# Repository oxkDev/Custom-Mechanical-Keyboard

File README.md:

# Custom-Mechanical-Keyboard
A custom low-profile 75% mechanical keyboard using a WeAct Blackpill v3.1 (STM32F411CEU6).

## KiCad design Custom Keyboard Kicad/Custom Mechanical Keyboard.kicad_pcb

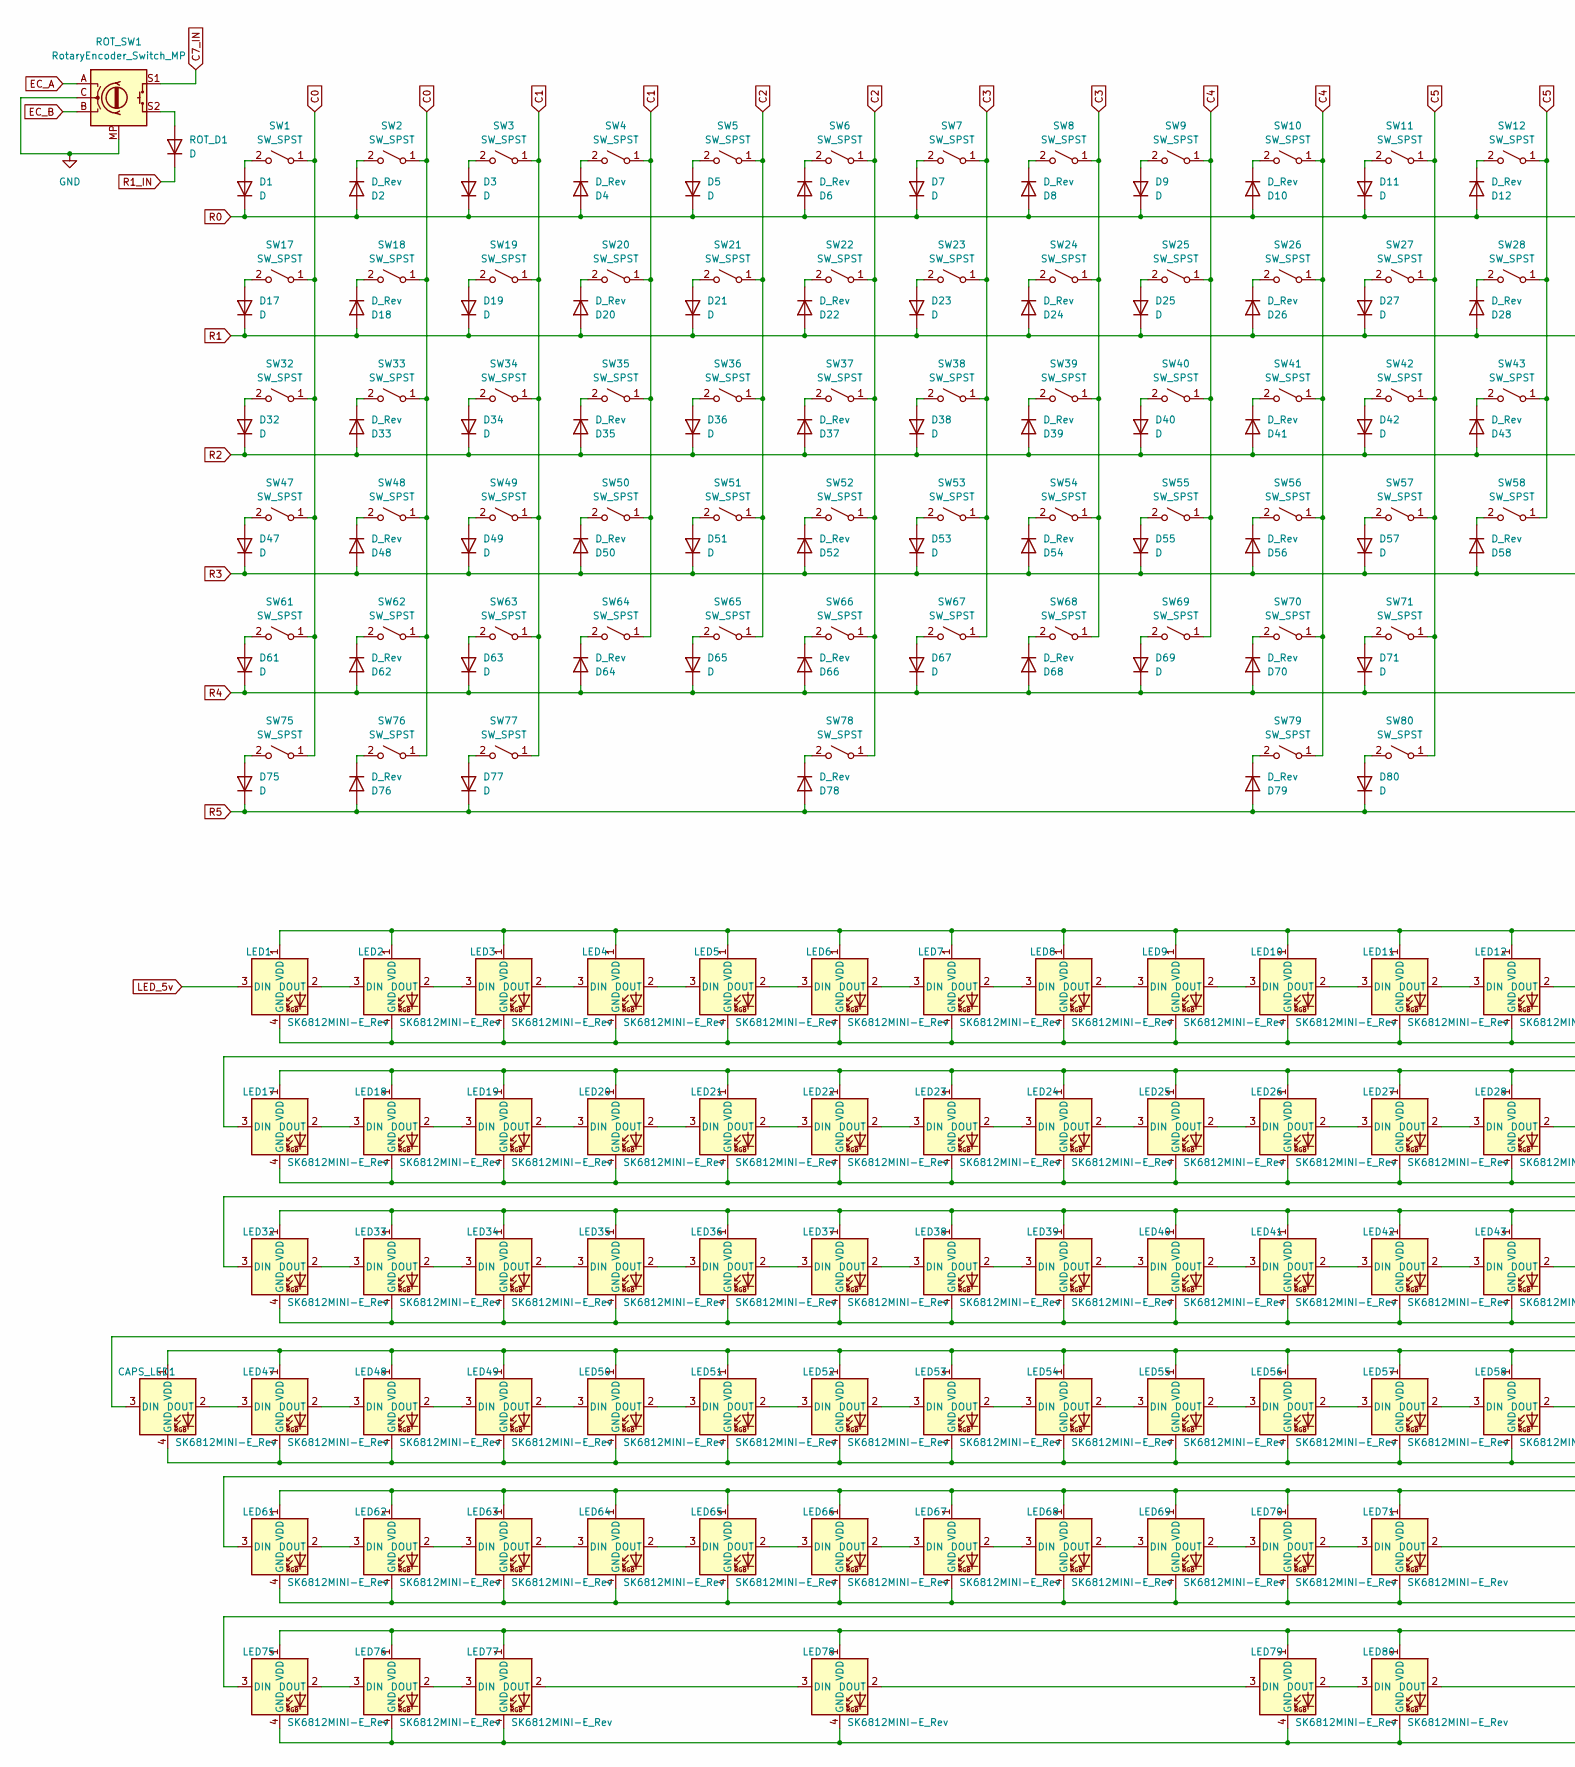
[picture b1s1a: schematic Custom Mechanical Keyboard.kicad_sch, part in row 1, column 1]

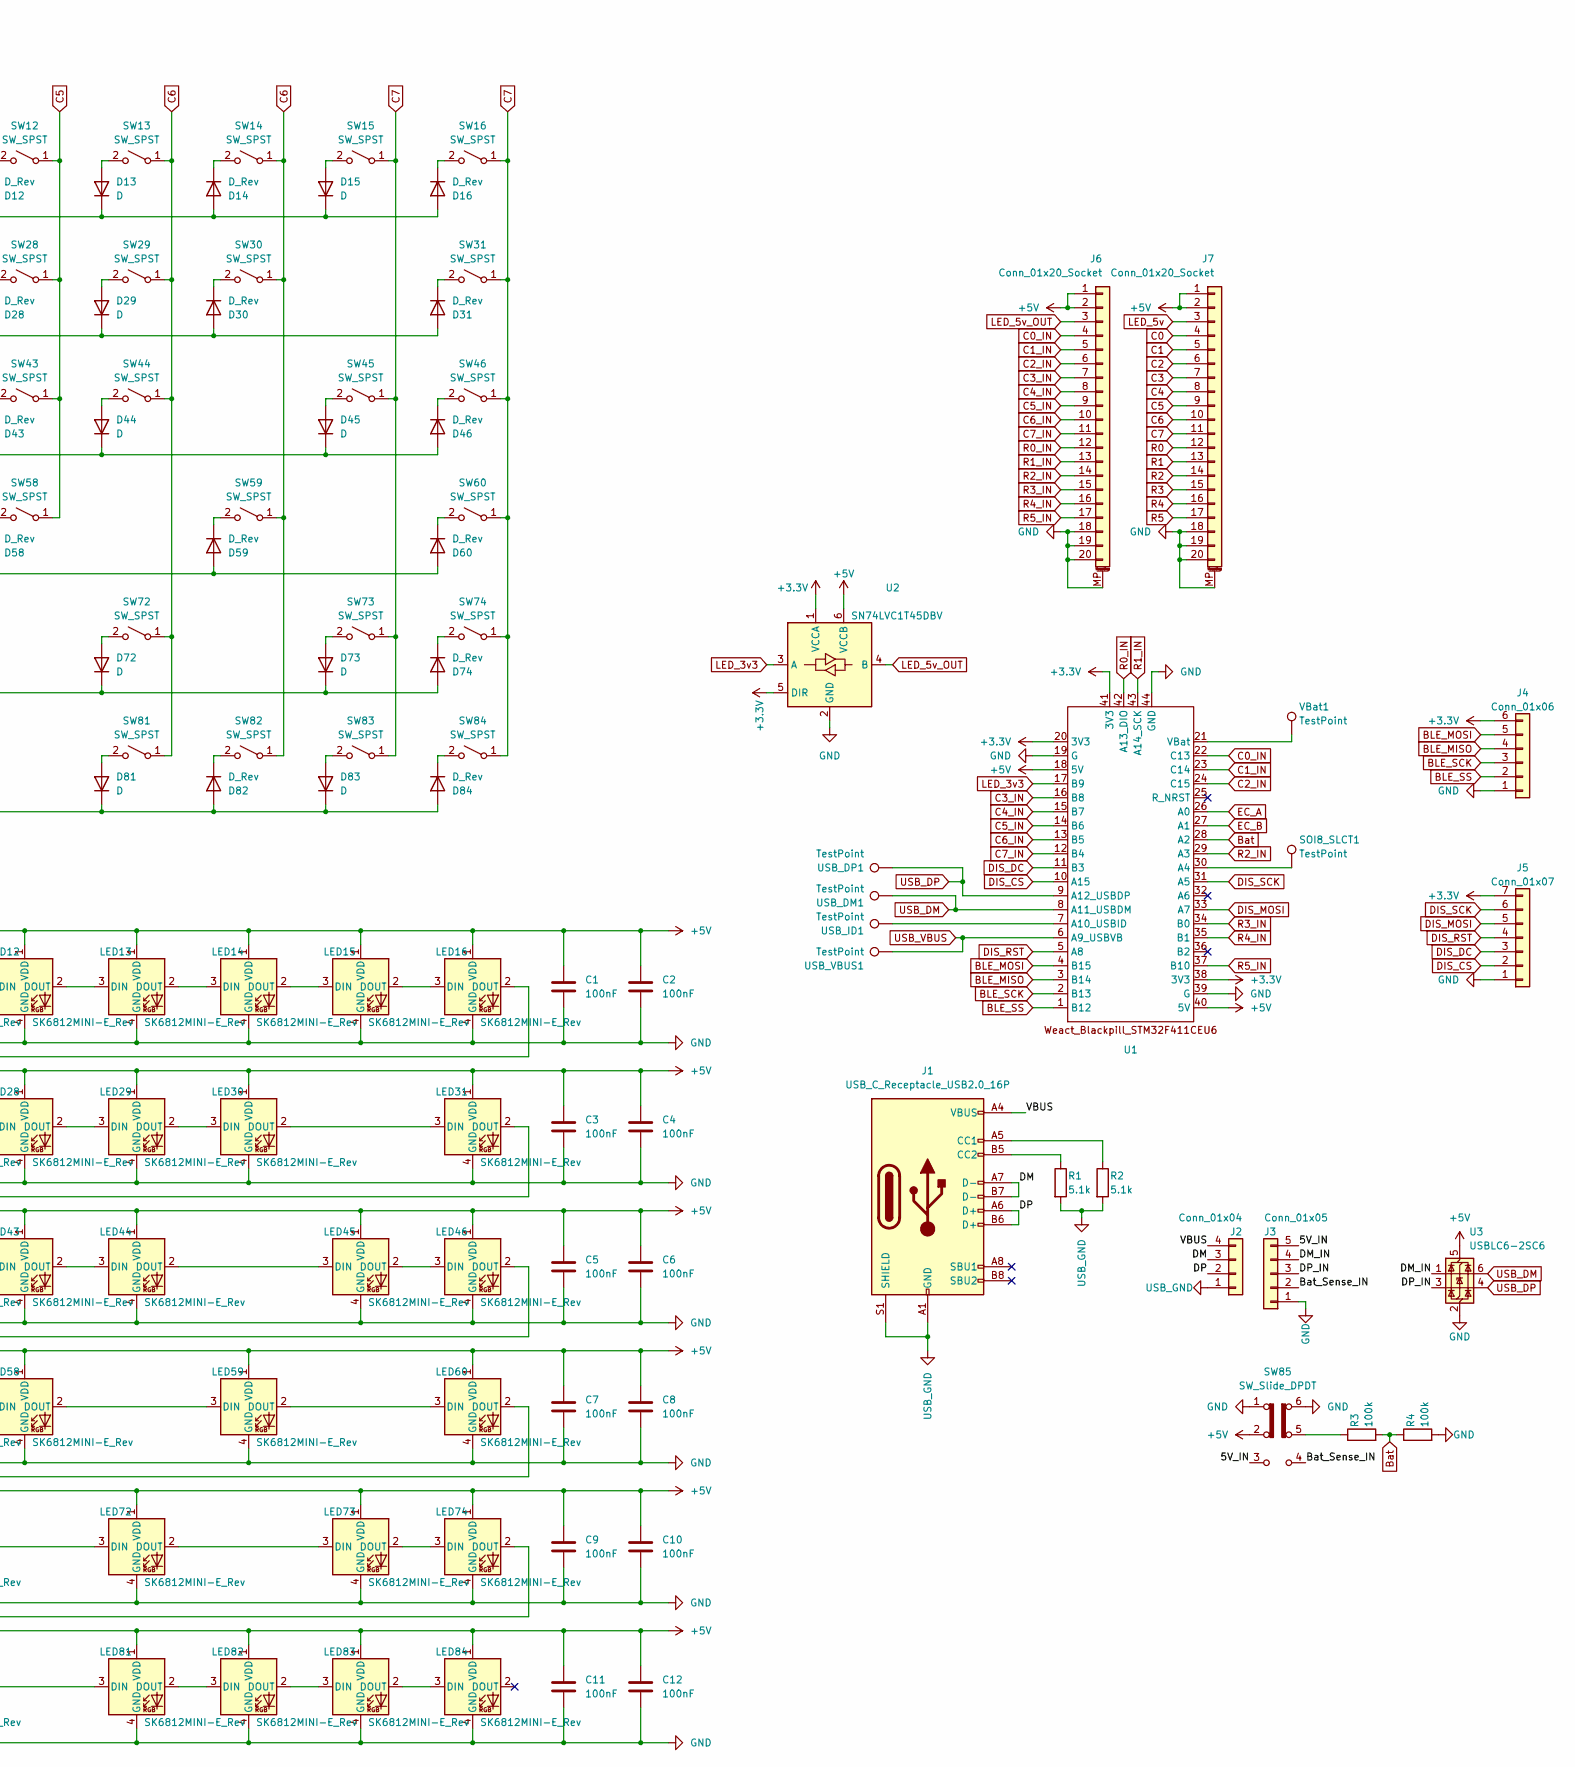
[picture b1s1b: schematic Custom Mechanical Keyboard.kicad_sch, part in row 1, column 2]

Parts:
C1, C2, C3, C4, C5, C6, C7, C8, C9, C10, C11, C12: 100nF; C_1206_3216Metric; MFG Part # GRM3195C2A104JA01D
CAPS_LED1: SK6812MINI-E_Rev; LED_SK6812MINI-E_Reversed_PLCC4_3.2x2.8mm_P1.5mm; MFG Part # SK6803MINI-E
D1, D3, D5, D7, D9, D11, D13, D15, D17, D19, D21, D23, D25, D27, D29, D32, D34, D36, D38, D40, D42, D44, D45, D47, D49, D51, D53, D55, D57, D61, D63, D65, D67, D69, D71, D72, D73, D75, D77, D80, D81, D83: D; D_SOD123; MFG Part # 1N4148W-F
D2, D4, D6, D8, D10, D12, D14, D16, D18, D20, D22, D24, D26, D28, D30, D31, D33, D35, D37, D39, D41, D43, D46, D48, D50, D52, D54, D56, D58, D59, D60, D62, D64, D66, D68, D70, D74, D76, D78, D79, D82, D84: D_Rev; D_SOD123_Rev; MFG Part # 1N4148W-F
J1: USB_C_Receptacle_USB2.0_16P; USB_C_Receptacle_HRO_TYPE-C-31-M-12; MFG Part # TYPE-C-31-M-14
J2: Conn_01x04; PinHeader_1x04_P2.00mm_Vertical
J3: Conn_01x05; PinHeader_1x05_P2.00mm_Vertical
J4: Conn_01x06; PinHeader_1x06_P2.00mm_Vertical
J5: Conn_01x07; PinHeader_1x07_P2.00mm_Vertical
J6, J7: Conn_01x20_Socket; XUNPU_FPC-05F-20PH20_1x20-1MP_P0.5mm_Horizontal; MFG Part # FPC-05F-20PH20
LED1, LED2, LED3, LED4, LED5, LED6, LED7, LED8, LED9, LED10, LED11, LED12, LED13, LED14, LED15, LED16, LED17, LED18, LED19, LED20, LED21, LED22, LED23, LED24, LED25, LED26, LED27, LED28, LED29, LED30, LED31, LED32, LED33, LED34, LED35, LED36, LED37, LED38, LED39, LED40, LED41, LED42, LED43, LED44, LED45, LED46, LED47, LED48, LED49, LED50, LED51, LED52, LED53, LED54, LED55, LED56, LED57, LED58, LED59, LED60, LED61, LED62, LED63, LED64, LED65, LED66, LED67, LED68, LED69, LED70, LED71, LED72, LED73, LED74, LED75, LED76, LED77, LED78, LED79, LED80, LED81, LED82, LED83, LED84: SK6812MINI-E_Rev; LED_SK6812MINI-E_Reversed_PLCC4_3.2x2.8mm_P1.5mm; MFG Part # SK6803MINI-E
R1, R2: 5.1k; R_1206_3216Metric_Pad1.30x1.75mm_HandSolder; MFG Part # ERJ-8ENF5101V
R3, R4: 100k; R_1206_3216Metric_Pad1.30x1.75mm_HandSolder; MFG Part # ERJ-U08D1003V
ROT_D1: D; D_SOD123; MFG Part # 1N4148W-F
ROT_SW1: RotaryEncoder_Switch_MP; RotaryEncoder_Alps_EC12E-Switch_Vertical_H20mm
SOI8_SLCT1: TestPoint; TestPoint_Pad_D1.0mm
SW1, SW2, SW3, SW4, SW5, SW6, SW7, SW8, SW9, SW10, SW11, SW12, SW13, SW14, SW15, SW16, SW17, SW18, SW19, SW20, SW21, SW22, SW23, SW24, SW25, SW26, SW27, SW28, SW29, SW30, SW31, SW32, SW33, SW34, SW35, SW36, SW37, SW38, SW39, SW40, SW41, SW42, SW43, SW44, SW45, SW46, SW47, SW48, SW49, SW50, SW51, SW52, SW53, SW54, SW55, SW56, SW57, SW58, SW59, SW60, SW61, SW62, SW63, SW64, SW65, SW66, SW67, SW68, SW69, SW70, SW71, SW72, SW73, SW74, SW75, SW76, SW77, SW78, SW79, SW80, SW81, SW82, SW83, SW84: SW_SPST; SW_MX_Kailh_Choc_V1V2_Mill-Max_Hybrid
SW85: SW_Slide_DPDT; SW_CK_JS202011AQN_DPDT_Angled; MFG Part # JS202011AQN
U1: Blackpill; STM32F4x1CxU6 WeActStudio
U2: SN74LVC1T45DBV; SOT-23-6; MFG Part # SN74LVC1T45DBV\
U3: USBLC6-2SC6; SOT-23-6; MFG Part # USBLC6-2SC6
USB_DM1: TestPoint; TestPoint_Pad_D1.0mm
USB_DP1: TestPoint; TestPoint_Pad_D1.0mm
USB_ID1: TestPoint; TestPoint_Pad_D1.0mm
USB_VBUS1: TestPoint; TestPoint_Pad_D1.0mm
VBat1: TestPoint; TestPoint_Pad_D1.0mm

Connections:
+3.3V: J4.6, J5.7, U1.20 (3V3), U1.38 (3V3), U1.41 (3V3), U2.1 (VCCA), U2.5 (DIR)
+5V: C1.1, C2.1, C3.1, C4.1, C5.1, C6.1, C7.1, C8.1, C9.1, C10.1, C11.1, C12.1, CAPS_LED1.1 (VDD), J6.1, J6.2, J7.1, J7.2, LED1.1 (VDD), LED2.1 (VDD), LED3.1 (VDD), LED4.1 (VDD), LED5.1 (VDD), LED6.1 (VDD), LED7.1 (VDD), LED8.1 (VDD), LED9.1 (VDD), LED10.1 (VDD), LED11.1 (VDD), LED12.1 (VDD), LED13.1 (VDD), LED14.1 (VDD), LED15.1 (VDD), LED16.1 (VDD), LED17.1 (VDD), LED18.1 (VDD), LED19.1 (VDD), LED20.1 (VDD), LED21.1 (VDD), LED22.1 (VDD), LED23.1 (VDD), LED24.1 (VDD), LED25.1 (VDD), LED26.1 (VDD), LED27.1 (VDD), LED28.1 (VDD), LED29.1 (VDD), LED30.1 (VDD), LED31.1 (VDD), LED32.1 (VDD), LED33.1 (VDD), LED34.1 (VDD), LED35.1 (VDD), LED36.1 (VDD), LED37.1 (VDD), LED38.1 (VDD), LED39.1 (VDD), LED40.1 (VDD), LED41.1 (VDD), LED42.1 (VDD), LED43.1 (VDD), LED44.1 (VDD), LED45.1 (VDD), LED46.1 (VDD), LED47.1 (VDD), LED48.1 (VDD), LED49.1 (VDD), LED50.1 (VDD), LED51.1 (VDD), LED52.1 (VDD), LED53.1 (VDD), LED54.1 (VDD), LED55.1 (VDD), LED56.1 (VDD), LED57.1 (VDD), LED58.1 (VDD), LED59.1 (VDD), LED60.1 (VDD), LED61.1 (VDD), LED62.1 (VDD), LED63.1 (VDD), LED64.1 (VDD), LED65.1 (VDD), LED66.1 (VDD), LED67.1 (VDD), LED68.1 (VDD), LED69.1 (VDD), LED70.1 (VDD), LED71.1 (VDD), LED72.1 (VDD), LED73.1 (VDD), LED74.1 (VDD), LED75.1 (VDD), LED76.1 (VDD), LED77.1 (VDD), LED78.1 (VDD), LED79.1 (VDD), LED80.1 (VDD), LED81.1 (VDD), LED82.1 (VDD), LED83.1 (VDD), LED84.1 (VDD), SW85.2 (B), U1.18 (5V), U1.40 (5V), U2.6 (VCCB), U3.5 (VBUS)
/5V_IN: J3.5, SW85.3 (C)
/Bat_Sense_IN: J3.2, SW85.4 (A)
/DM: J1.A7 (D-), J1.B7 (D-), J2.3
/DM_IN: J3.4, U3.1 (I/O1)
/DP: J1.A6 (D+), J1.B6 (D+), J2.2
/DP_IN: J3.3, U3.3 (I/O2)
/VBUS: J1.A4 (VBUS), J1.A9 (VBUS), J1.B4 (VBUS), J1.B9 (VBUS), J2.4
BLE_MISO: J4.4, U1.3 (B14)
BLE_MOSI: J4.5, U1.4 (B15)
BLE_SCK: J4.3, U1.2 (B13)
BLE_SS: J4.2, U1.1 (B12)
Bat: R3.2, R4.1, U1.28 (A2)
C0: J7.4, SW1.1 (A), SW2.1 (A), SW17.1 (A), SW18.1 (A), SW32.1 (A), SW33.1 (A), SW47.1 (A), SW48.1 (A), SW61.1 (A), SW62.1 (A), SW75.1 (A), SW76.1 (A)
C0_IN: J6.4, U1.22 (C13)
C1: J7.5, SW3.1 (A), SW4.1 (A), SW19.1 (A), SW20.1 (A), SW34.1 (A), SW35.1 (A), SW49.1 (A), SW50.1 (A), SW63.1 (A), SW64.1 (A), SW77.1 (A)
C1_IN: J6.5, U1.23 (C14)
C2: J7.6, SW5.1 (A), SW6.1 (A), SW21.1 (A), SW22.1 (A), SW36.1 (A), SW37.1 (A), SW51.1 (A), SW52.1 (A), SW65.1 (A), SW66.1 (A), SW78.1 (A)
C2_IN: J6.6, U1.24 (C15)
C3: J7.7, SW7.1 (A), SW8.1 (A), SW23.1 (A), SW24.1 (A), SW38.1 (A), SW39.1 (A), SW53.1 (A), SW54.1 (A), SW67.1 (A), SW68.1 (A)
C3_IN: J6.7, U1.16 (B8)
C4: J7.8, SW9.1 (A), SW10.1 (A), SW25.1 (A), SW26.1 (A), SW40.1 (A), SW41.1 (A), SW55.1 (A), SW56.1 (A), SW69.1 (A), SW70.1 (A), SW79.1 (A)
C4_IN: J6.8, U1.15 (B7)
C5: J7.9, SW11.1 (A), SW12.1 (A), SW27.1 (A), SW28.1 (A), SW42.1 (A), SW43.1 (A), SW57.1 (A), SW58.1 (A), SW71.1 (A), SW80.1 (A)
C5_IN: J6.9, U1.14 (B6)
C6: J7.10, SW13.1 (A), SW14.1 (A), SW29.1 (A), SW30.1 (A), SW44.1 (A), SW59.1 (A), SW72.1 (A), SW81.1 (A), SW82.1 (A)
C6_IN: J6.10, U1.13 (B5)
C7: J7.11, SW15.1 (A), SW16.1 (A), SW31.1 (A), SW45.1 (A), SW46.1 (A), SW60.1 (A), SW73.1 (A), SW74.1 (A), SW83.1 (A), SW84.1 (A)
C7_IN: J6.11, ROT_SW1.S1, U1.12 (B4)
DIS_CS: J5.2, U1.10 (A15)
DIS_DC: J5.3, U1.11 (B3)
DIS_MOSI: J5.5, U1.33 (A7)
DIS_RST: J5.4, U1.5 (A8)
DIS_SCK: J5.6, U1.31 (A5)
EC_A: ROT_SW1.A, U1.26 (A0)
EC_B: ROT_SW1.B, U1.27 (A1)
GND: C1.2, C2.2, C3.2, C4.2, C5.2, C6.2, C7.2, C8.2, C9.2, C10.2, C11.2, C12.2, CAPS_LED1.4 (GND), J3.1, J4.1, J5.1, J6.18, J6.19, J6.20, J6.MP (MountPin), J7.18, J7.19, J7.20, J7.MP (MountPin), LED1.4 (GND), LED2.4 (GND), LED3.4 (GND), LED4.4 (GND), LED5.4 (GND), LED6.4 (GND), LED7.4 (GND), LED8.4 (GND), LED9.4 (GND), LED10.4 (GND), LED11.4 (GND), LED12.4 (GND), LED13.4 (GND), LED14.4 (GND), LED15.4 (GND), LED16.4 (GND), LED17.4 (GND), LED18.4 (GND), LED19.4 (GND), LED20.4 (GND), LED21.4 (GND), LED22.4 (GND), LED23.4 (GND), LED24.4 (GND), LED25.4 (GND), LED26.4 (GND), LED27.4 (GND), LED28.4 (GND), LED29.4 (GND), LED30.4 (GND), LED31.4 (GND), LED32.4 (GND), LED33.4 (GND), LED34.4 (GND), LED35.4 (GND), LED36.4 (GND), LED37.4 (GND), LED38.4 (GND), LED39.4 (GND), LED40.4 (GND), LED41.4 (GND), LED42.4 (GND), LED43.4 (GND), LED44.4 (GND), LED45.4 (GND), LED46.4 (GND), LED47.4 (GND), LED48.4 (GND), LED49.4 (GND), LED50.4 (GND), LED51.4 (GND), LED52.4 (GND), LED53.4 (GND), LED54.4 (GND), LED55.4 (GND), LED56.4 (GND), LED57.4 (GND), LED58.4 (GND), LED59.4 (GND), LED60.4 (GND), LED61.4 (GND), LED62.4 (GND), LED63.4 (GND), LED64.4 (GND), LED65.4 (GND), LED66.4 (GND), LED67.4 (GND), LED68.4 (GND), LED69.4 (GND), LED70.4 (GND), LED71.4 (GND), LED72.4 (GND), LED73.4 (GND), LED74.4 (GND), LED75.4 (GND), LED76.4 (GND), LED77.4 (GND), LED78.4 (GND), LED79.4 (GND), LED80.4 (GND), LED81.4 (GND), LED82.4 (GND), LED83.4 (GND), LED84.4 (GND), R4.2, ROT_SW1.C, ROT_SW1.MP, SW85.1 (A), SW85.6 (C), U1.19 (G), U1.39 (G), U1.44 (GND), U2.2 (GND), U3.2 (GND)
LED_3v3: U1.17 (B9), U2.3 (A)
LED_5v: J7.3, LED1.3 (DIN)
LED_5v_OUT: J6.3, U2.4 (B)
unnamed: CAPS_LED1.3 (DIN), LED46.2 (DOUT)
unnamed: CAPS_LED1.2 (DOUT), LED47.3 (DIN)
unnamed: D1.2 (A), SW1.2 (B)
unnamed: D2.1 (K), SW2.2 (B)
unnamed: D3.2 (A), SW3.2 (B)
unnamed: D4.1 (K), SW4.2 (B)
unnamed: D5.2 (A), SW5.2 (B)
unnamed: D6.1 (K), SW6.2 (B)
unnamed: D7.2 (A), SW7.2 (B)
unnamed: D8.1 (K), SW8.2 (B)
unnamed: D9.2 (A), SW9.2 (B)
unnamed: D10.1 (K), SW10.2 (B)
unnamed: D11.2 (A), SW11.2 (B)
unnamed: D12.1 (K), SW12.2 (B)
unnamed: D13.2 (A), SW13.2 (B)
unnamed: D14.1 (K), SW14.2 (B)
unnamed: D15.2 (A), SW15.2 (B)
unnamed: D16.1 (K), SW16.2 (B)
unnamed: D17.2 (A), SW17.2 (B)
unnamed: D18.1 (K), SW18.2 (B)
unnamed: D19.2 (A), SW19.2 (B)
unnamed: D20.1 (K), SW20.2 (B)
unnamed: D21.2 (A), SW21.2 (B)
unnamed: D22.1 (K), SW22.2 (B)
unnamed: D23.2 (A), SW23.2 (B)
unnamed: D24.1 (K), SW24.2 (B)
unnamed: D25.2 (A), SW25.2 (B)
unnamed: D26.1 (K), SW26.2 (B)
unnamed: D27.2 (A), SW27.2 (B)
unnamed: D28.1 (K), SW28.2 (B)
unnamed: D29.2 (A), SW29.2 (B)
unnamed: D30.1 (K), SW30.2 (B)
unnamed: D31.1 (K), SW31.2 (B)
unnamed: D32.2 (A), SW32.2 (B)
unnamed: D33.1 (K), SW33.2 (B)
unnamed: D34.2 (A), SW34.2 (B)
unnamed: D35.1 (K), SW35.2 (B)
unnamed: D36.2 (A), SW36.2 (B)
unnamed: D37.1 (K), SW37.2 (B)
unnamed: D38.2 (A), SW38.2 (B)
unnamed: D39.1 (K), SW39.2 (B)
unnamed: D40.2 (A), SW40.2 (B)
unnamed: D41.1 (K), SW41.2 (B)
unnamed: D42.2 (A), SW42.2 (B)
unnamed: D43.1 (K), SW43.2 (B)
unnamed: D44.2 (A), SW44.2 (B)
unnamed: D45.2 (A), SW45.2 (B)
unnamed: D46.1 (K), SW46.2 (B)
unnamed: D47.2 (A), SW47.2 (B)
unnamed: D48.1 (K), SW48.2 (B)
unnamed: D49.2 (A), SW49.2 (B)
unnamed: D50.1 (K), SW50.2 (B)
unnamed: D51.2 (A), SW51.2 (B)
unnamed: D52.1 (K), SW52.2 (B)
unnamed: D53.2 (A), SW53.2 (B)
unnamed: D54.1 (K), SW54.2 (B)
unnamed: D55.2 (A), SW55.2 (B)
unnamed: D56.1 (K), SW56.2 (B)
unnamed: D57.2 (A), SW57.2 (B)
unnamed: D58.1 (K), SW58.2 (B)
unnamed: D59.1 (K), SW59.2 (B)
unnamed: D60.1 (K), SW60.2 (B)
unnamed: D61.2 (A), SW61.2 (B)
unnamed: D62.1 (K), SW62.2 (B)
unnamed: D63.2 (A), SW63.2 (B)
unnamed: D64.1 (K), SW64.2 (B)
unnamed: D65.2 (A), SW65.2 (B)
unnamed: D66.1 (K), SW66.2 (B)
unnamed: D67.2 (A), SW67.2 (B)
unnamed: D68.1 (K), SW68.2 (B)
unnamed: D69.2 (A), SW69.2 (B)
unnamed: D70.1 (K), SW70.2 (B)
unnamed: D71.2 (A), SW71.2 (B)
unnamed: D72.2 (A), SW72.2 (B)
unnamed: D73.2 (A), SW73.2 (B)
unnamed: D74.1 (K), SW74.2 (B)
unnamed: D75.2 (A), SW75.2 (B)
unnamed: D76.1 (K), SW76.2 (B)
unnamed: D77.2 (A), SW77.2 (B)
unnamed: D78.1 (K), SW78.2 (B)
unnamed: D79.1 (K), SW79.2 (B)
unnamed: D80.2 (A), SW80.2 (B)
unnamed: D81.2 (A), SW81.2 (B)
unnamed: D82.1 (K), SW82.2 (B)
unnamed: D83.2 (A), SW83.2 (B)
unnamed: D84.1 (K), SW84.2 (B)
unnamed: J1.A5 (CC1), R2.1
unnamed: J1.B5 (CC2), R1.1
unnamed: LED1.2 (DOUT), LED2.3 (DIN)
unnamed: LED2.2 (DOUT), LED3.3 (DIN)
unnamed: LED3.2 (DOUT), LED4.3 (DIN)
unnamed: LED4.2 (DOUT), LED5.3 (DIN)
unnamed: LED5.2 (DOUT), LED6.3 (DIN)
unnamed: LED6.2 (DOUT), LED7.3 (DIN)
unnamed: LED7.2 (DOUT), LED8.3 (DIN)
unnamed: LED8.2 (DOUT), LED9.3 (DIN)
unnamed: LED9.2 (DOUT), LED10.3 (DIN)
unnamed: LED10.2 (DOUT), LED11.3 (DIN)
unnamed: LED11.2 (DOUT), LED12.3 (DIN)
unnamed: LED12.2 (DOUT), LED13.3 (DIN)
unnamed: LED13.2 (DOUT), LED14.3 (DIN)
unnamed: LED14.2 (DOUT), LED15.3 (DIN)
unnamed: LED15.2 (DOUT), LED16.3 (DIN)
unnamed: LED16.2 (DOUT), LED17.3 (DIN)
unnamed: LED17.2 (DOUT), LED18.3 (DIN)
unnamed: LED18.2 (DOUT), LED19.3 (DIN)
unnamed: LED19.2 (DOUT), LED20.3 (DIN)
unnamed: LED20.2 (DOUT), LED21.3 (DIN)
unnamed: LED21.2 (DOUT), LED22.3 (DIN)
unnamed: LED22.2 (DOUT), LED23.3 (DIN)
unnamed: LED23.2 (DOUT), LED24.3 (DIN)
unnamed: LED24.2 (DOUT), LED25.3 (DIN)
unnamed: LED25.2 (DOUT), LED26.3 (DIN)
unnamed: LED26.2 (DOUT), LED27.3 (DIN)
unnamed: LED27.2 (DOUT), LED28.3 (DIN)
unnamed: LED28.2 (DOUT), LED29.3 (DIN)
unnamed: LED29.2 (DOUT), LED30.3 (DIN)
unnamed: LED30.2 (DOUT), LED31.3 (DIN)
unnamed: LED31.2 (DOUT), LED32.3 (DIN)
unnamed: LED32.2 (DOUT), LED33.3 (DIN)
unnamed: LED33.2 (DOUT), LED34.3 (DIN)
unnamed: LED34.2 (DOUT), LED35.3 (DIN)
unnamed: LED35.2 (DOUT), LED36.3 (DIN)
unnamed: LED36.2 (DOUT), LED37.3 (DIN)
unnamed: LED37.2 (DOUT), LED38.3 (DIN)
unnamed: LED38.2 (DOUT), LED39.3 (DIN)
unnamed: LED39.2 (DOUT), LED40.3 (DIN)
unnamed: LED40.2 (DOUT), LED41.3 (DIN)
unnamed: LED41.2 (DOUT), LED42.3 (DIN)
unnamed: LED42.2 (DOUT), LED43.3 (DIN)
unnamed: LED43.2 (DOUT), LED44.3 (DIN)
unnamed: LED44.2 (DOUT), LED45.3 (DIN)
unnamed: LED45.2 (DOUT), LED46.3 (DIN)
unnamed: LED47.2 (DOUT), LED48.3 (DIN)
unnamed: LED48.2 (DOUT), LED49.3 (DIN)
unnamed: LED49.2 (DOUT), LED50.3 (DIN)
unnamed: LED50.2 (DOUT), LED51.3 (DIN)
unnamed: LED51.2 (DOUT), LED52.3 (DIN)
unnamed: LED52.2 (DOUT), LED53.3 (DIN)
unnamed: LED53.2 (DOUT), LED54.3 (DIN)
unnamed: LED54.2 (DOUT), LED55.3 (DIN)
unnamed: LED55.2 (DOUT), LED56.3 (DIN)
unnamed: LED56.2 (DOUT), LED57.3 (DIN)
unnamed: LED57.2 (DOUT), LED58.3 (DIN)
unnamed: LED58.2 (DOUT), LED59.3 (DIN)
unnamed: LED59.2 (DOUT), LED60.3 (DIN)
unnamed: LED60.2 (DOUT), LED61.3 (DIN)
unnamed: LED61.2 (DOUT), LED62.3 (DIN)
unnamed: LED62.2 (DOUT), LED63.3 (DIN)
unnamed: LED63.2 (DOUT), LED64.3 (DIN)
unnamed: LED64.2 (DOUT), LED65.3 (DIN)
unnamed: LED65.2 (DOUT), LED66.3 (DIN)
unnamed: LED66.2 (DOUT), LED67.3 (DIN)
unnamed: LED67.2 (DOUT), LED68.3 (DIN)
unnamed: LED68.2 (DOUT), LED69.3 (DIN)
unnamed: LED69.2 (DOUT), LED70.3 (DIN)
unnamed: LED70.2 (DOUT), LED71.3 (DIN)
unnamed: LED71.2 (DOUT), LED72.3 (DIN)
unnamed: LED72.2 (DOUT), LED73.3 (DIN)
unnamed: LED73.2 (DOUT), LED74.3 (DIN)
unnamed: LED74.2 (DOUT), LED75.3 (DIN)
unnamed: LED75.2 (DOUT), LED76.3 (DIN)
unnamed: LED76.2 (DOUT), LED77.3 (DIN)
unnamed: LED77.2 (DOUT), LED78.3 (DIN)
unnamed: LED78.2 (DOUT), LED79.3 (DIN)
unnamed: LED79.2 (DOUT), LED80.3 (DIN)
unnamed: LED80.2 (DOUT), LED81.3 (DIN)
unnamed: LED81.2 (DOUT), LED82.3 (DIN)
unnamed: LED82.2 (DOUT), LED83.3 (DIN)
unnamed: LED83.2 (DOUT), LED84.3 (DIN)
unnamed: R3.1, SW85.5 (B)
unnamed: ROT_D1.2 (A), ROT_SW1.S2
unnamed: SOI8_SLCT1.1, U1.30 (A4)
unnamed: U1.7 (A10_USBID), USB_ID1.1
unnamed: U1.21 (VBat), VBat1.1
R0: D1.1 (K), D2.2 (A), D3.1 (K), D4.2 (A), D5.1 (K), D6.2 (A), D7.1 (K), D8.2 (A), D9.1 (K), D10.2 (A), D11.1 (K), D12.2 (A), D13.1 (K), D14.2 (A), D15.1 (K), D16.2 (A), J7.12
R0_IN: J6.12, U1.42 (A13_DIO)
R1: D17.1 (K), D18.2 (A), D19.1 (K), D20.2 (A), D21.1 (K), D22.2 (A), D23.1 (K), D24.2 (A), D25.1 (K), D26.2 (A), D27.1 (K), D28.2 (A), D29.1 (K), D30.2 (A), D31.2 (A), J7.13
R1_IN: J6.13, ROT_D1.1 (K), U1.43 (A14_SCK)
R2: D32.1 (K), D33.2 (A), D34.1 (K), D35.2 (A), D36.1 (K), D37.2 (A), D38.1 (K), D39.2 (A), D40.1 (K), D41.2 (A), D42.1 (K), D43.2 (A), D44.1 (K), D45.1 (K), D46.2 (A), J7.14
R2_IN: J6.14, U1.29 (A3)
R3: D47.1 (K), D48.2 (A), D49.1 (K), D50.2 (A), D51.1 (K), D52.2 (A), D53.1 (K), D54.2 (A), D55.1 (K), D56.2 (A), D57.1 (K), D58.2 (A), D59.2 (A), D60.2 (A), J7.15
R3_IN: J6.15, U1.34 (B0)
R4: D61.1 (K), D62.2 (A), D63.1 (K), D64.2 (A), D65.1 (K), D66.2 (A), D67.1 (K), D68.2 (A), D69.1 (K), D70.2 (A), D71.1 (K), D72.1 (K), D73.1 (K), D74.2 (A), J7.16
R4_IN: J6.16, U1.35 (B1)
R5: D75.1 (K), D76.2 (A), D77.1 (K), D78.2 (A), D79.2 (A), D80.1 (K), D81.1 (K), D82.2 (A), D83.1 (K), D84.2 (A), J7.17
R5_IN: J6.17, U1.37 (B10)
USB_DM: U1.8 (A11_USBDM), U3.6 (I/O1), USB_DM1.1
USB_DP: U1.9 (A12_USBDP), U3.4 (I/O2), USB_DP1.1
USB_GND: J1.A1 (GND), J1.A12 (GND), J1.B1 (GND), J1.B12 (GND), J1.S1 (SHIELD), J2.1, R1.2, R2.2
USB_VBUS: U1.6 (A9_USBVB), USB_VBUS1.1

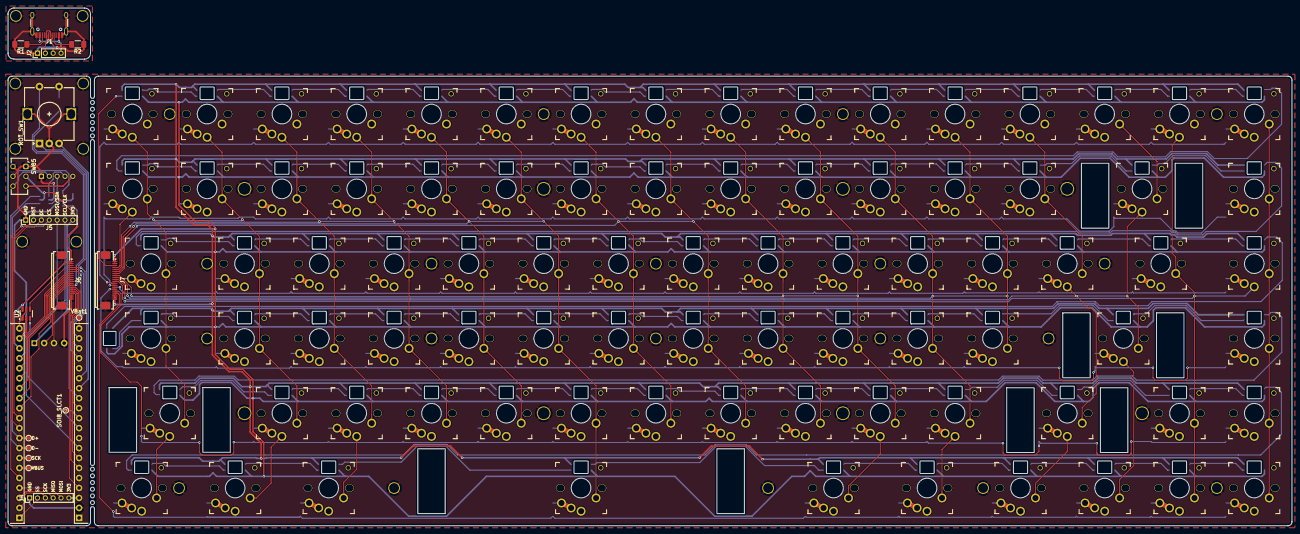
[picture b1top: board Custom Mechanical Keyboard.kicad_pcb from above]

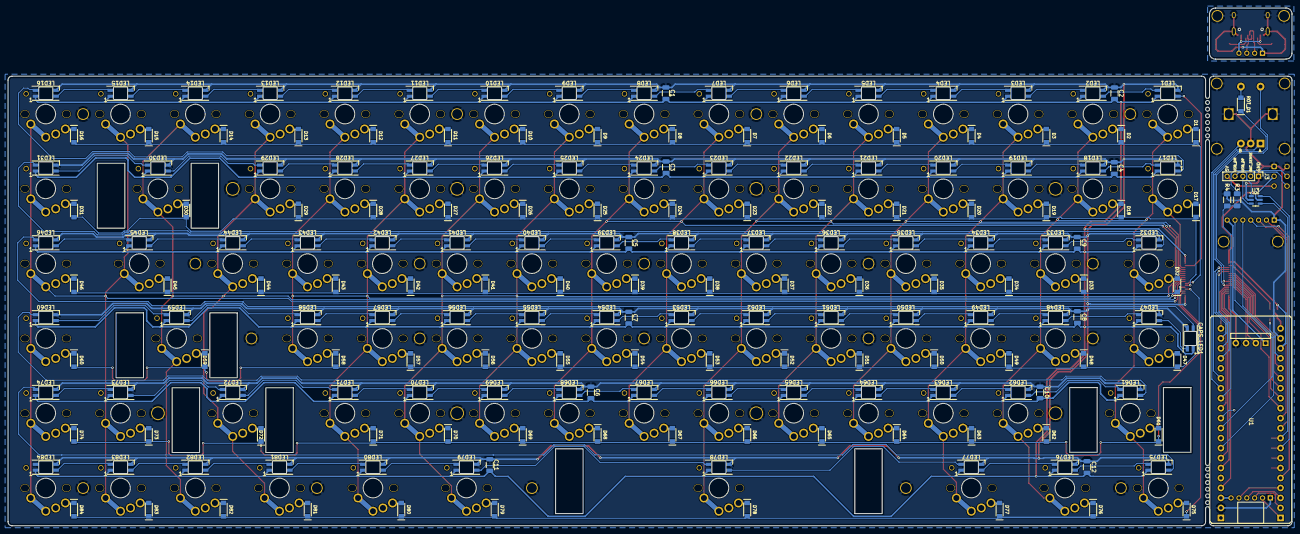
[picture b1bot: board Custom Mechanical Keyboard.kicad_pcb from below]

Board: 2 copper layers, 327.0 x 114.5 mm, 288 parts (187 on the bottom side), 232 nets.

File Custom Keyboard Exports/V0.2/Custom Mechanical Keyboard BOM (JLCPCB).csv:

Designator,Qty,Type,Manufacturer,Comment,Footprint,Description
"C1,C2,C3,C4,C5,C6,C7,C8,C9,C10,C11,C12",12,SMD,Murata Electronics,GRM3195C2A104JA01D,Capacitor_SMD:C_1206_3216Metric,Multilayer Ceramic Capacitors MLCC - SMD/SMT 0.1 uF 100 VDC 5% 1206 C0G (NP0)
CAPS_LED1,1,SMD,Shenzhen Normand Electronic,SK6803MINI-E,LED_SMD:LED_SK6812MINI-E_PLCC4_3.2x2.8mm_P1.5mm_1,3.2x2.8x1.78 mm 0.2W Intelligent external control surface  mount SMD LED (Facing away from PCB)
"J6,J7",2,SMD,Xunpu,FPC-05F-20PH20,PCM_marbastlib-various:XUNPU_FPC-05F-20PH20_1x20-1MP_P0.5mm_Horizontal,"Generic connectable mounting pin connector, single row, 01x20, script generated (kicad-library-utils/schlib/autogen/connector/)"
"LED1,LED2,LED3,LED4,LED5,LED6,LED7,LED8,LED9,LED10,LED11,LED12,LED13,LED14,LED15,LED16,LED17,LED18,LED19,LED20,LED21,LED22,LED23,LED24,LED25,LED26,LED27,LED28,LED29,LED30,LED31,LED32,LED33,LED34,LED35,LED36,LED37,LED38,LED39,LED40,LED41,LED42,LED43,LED44,LED45,LED46,LED47,LED48,LED49,LED50,LED51,LED52,LED53,LED54,LED55,LED56,LED57,LED58,LED59,LED60,LED61,LED62,LED63,LED64,LED65,LED66,LED67,LED68,LED69,LED70,LED71,LED72,LED73,LED74,LED75,LED76,LED77,LED78,LED79,LED80,LED81,LED82,LED83,LED84",84,SMD,Shenzhen Normand Electronic,SK6803MINI-E,LED_SMD:LED_SK6812MINI-E_Reversed_PLCC4_3.2x2.8mm_P1.5mm,3.2x2.8x1.78 mm 0.2W Intelligent external control surface  mount SMD LED (Facing into PCB)
"R3,R4",2,SMD,Panasonic,ERJ-U08D1003V,Resistor_SMD:R_1206_3216Metric_Pad1.30x1.75mm_HandSolder,Thick Film Resistors - SMD 1206 0.5% 100kOhm Anti-Sulfur AEC-Q200
SW85,1,Thru-Hole,C&K,JS202011AQN,Button_Switch_THT:SW_CK_JS202011AQN_DPDT_Angled,SWITCH SLIDE DPDT 300MA 6V
U2,1,SMD,Texas Instruments,TXS0101DBV,Package_TO_SOT_SMD:SOT-23-6,"1-Bit Bidirectional Voltage-Level Shifter for Open-Drain and Push-Pull Application, SOT-23"
U3,1,SMD,STMicroelectronics,USBLC6-2SC6,Package_TO_SOT_SMD:SOT-23-6,"Very low capacitance ESD protection diode, 2 data-line, SOT-23-6"
"D1,D3,D5,D7,D9,D11,D13,D15,D17,D19,D21,D23,D25,D27,D29,D32,D34,D36,D38,D40,D42,D44,D45,D47,D49,D51,D53,D55,D57,D61,D63,D65,D67,D69,D71,D72,D73,D75,D77,D80,D81,D83,ROT_D1",43,SMD,Diodes Incorporated,1N4148W-F,Keyboard_Parts_Footprint:D_SOD123,Small Signal Switching Diodes 400mW 100Vrrm 4ns
"D2,D4,D6,D8,D10,D12,D14,D16,D18,D20,D22,D24,D26,D28,D30,D31,D33,D35,D37,D39,D41,D43,D46,D48,D50,D52,D54,D56,D58,D59,D60,D62,D64,D66,D68,D70,D74,D76,D78,D79,D82,D84",42,SMD,Diodes Incorporated,1N4148W-F,Keyboard_Parts_Footprint:D_SOD123_Rev,Small Signal Switching Diodes 400mW 100Vrrm 4ns

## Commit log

2025-09-28 update files
2025-09-30 Changed MCU position, swapped screw-in stab mounts for stab cutouts for gateron lp stabilizers
2025-10-03 Updated wiring, board size, and added rotary encoder and usbc recepticle with esd protection as separate board
2025-10-05 Fixed matrix LED wiring, shifted LED 0.2mm closer to switch. Changed capslock LED to addressable LED connected to matrix LED array.
2025-10-07 Added custom layout json
2025-10-07 Added missing readme and removed firmware folder.
2025-10-15 Added all ports: USB, display (SPI), BLE (SPI). Fixed all main errors in DRC. Added power switch (linked to power input for board).
2025-10-16 Commit before export
2025-10-16 Rewired rotary encoder, battery and row pins for space efficiency. Commit before export.
2025-10-20 Separated MCU and matrix boards, To be connected using FPC.
2025-10-22 Finished separate MCU and keyboard matrix boards, Added ribbon cable connectors and adjusted tracks to fit 0.05mm tolerance positioning. DRC checked, ready for export.
2025-10-24 Fixed DRC issues, shifted MCU side FPC connector to face opposite way (ribbon cable goes around and under MCU pcb).
2025-10-25 feat: Added connection points between MCU and matrix pcb, and indicated v-cut point, generated export for JLCPCB.
2025-10-26 fix: Made mouse bites instead of v-cut, commit before seperate pcb export.
2025-10-26 feat: Swapped capslock LED to bottom (same as LED matrix)
2025-11-03 Commit after exports
2025-11-09 Feat: Changed level shifter from TXS0101DBV to SN74LVC1T45DBV, footprint and wiring not changed.
2025-11-11 Feat: Added USB PCB, edited PCM Master Lib sunken usb-c port - changed pcb edge line to drawing to allow for edge cut line connection
2025-11-11 Fix: Changed USB C receptacle to 31M12 instead of 31M14 to fit cheaper assembly requirements
2025-11-11 Feat: Generated export for USB Plug
